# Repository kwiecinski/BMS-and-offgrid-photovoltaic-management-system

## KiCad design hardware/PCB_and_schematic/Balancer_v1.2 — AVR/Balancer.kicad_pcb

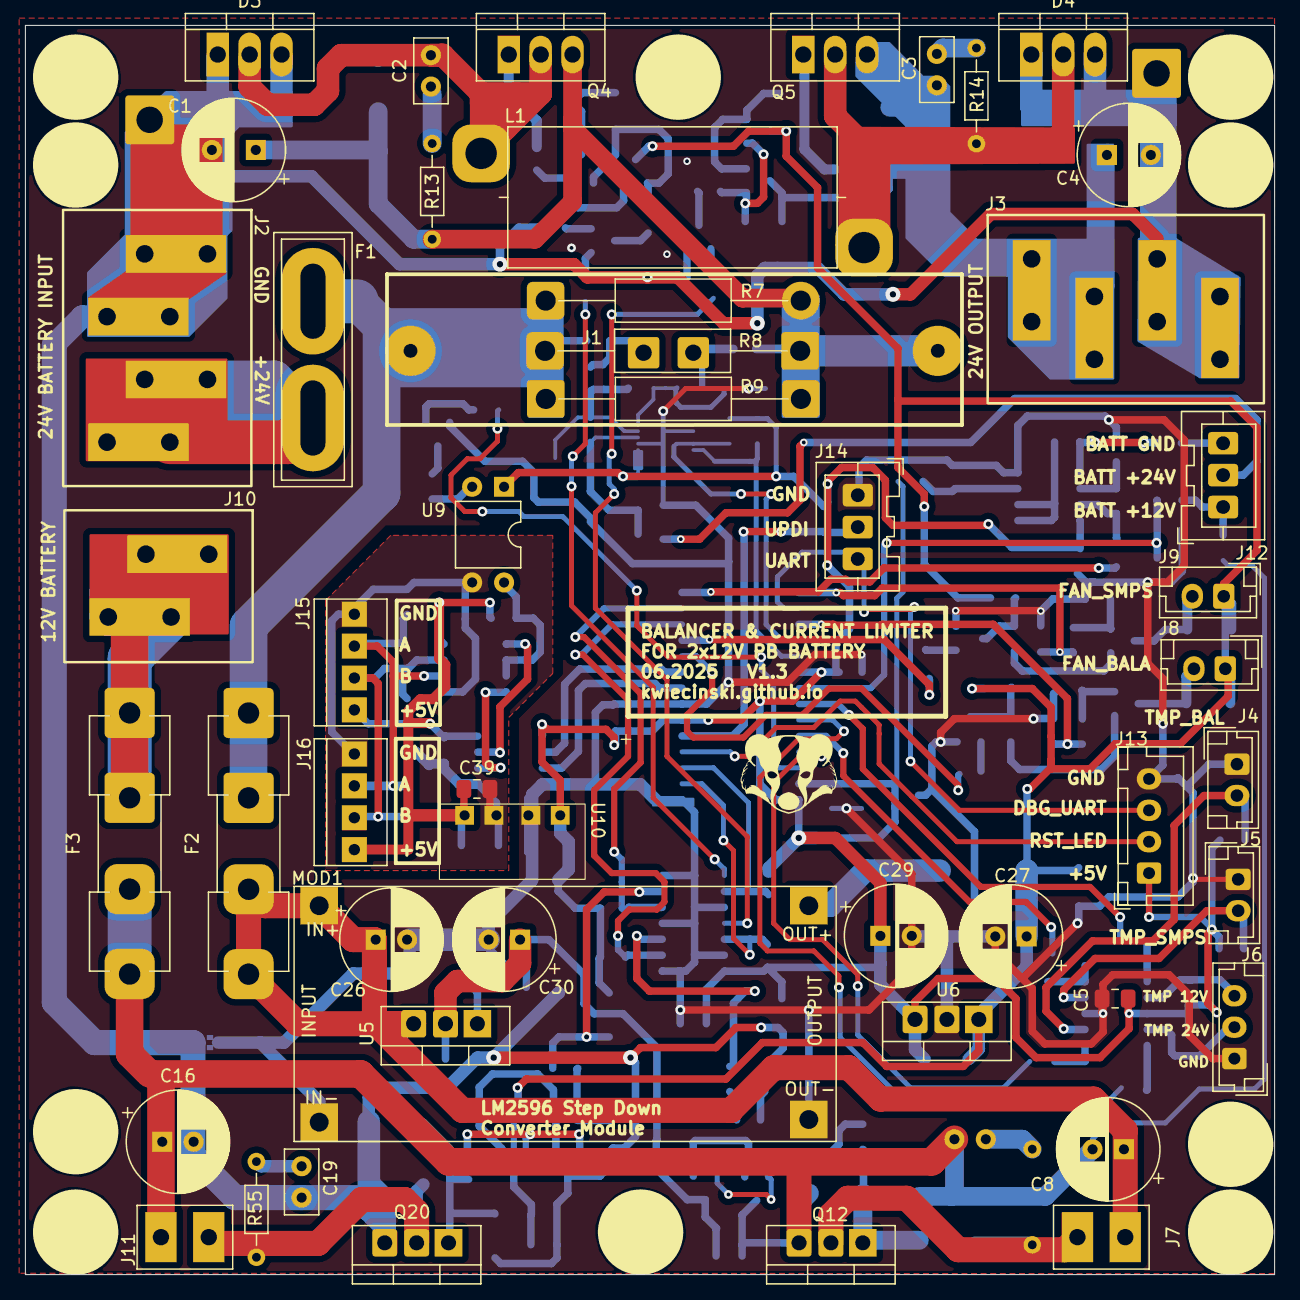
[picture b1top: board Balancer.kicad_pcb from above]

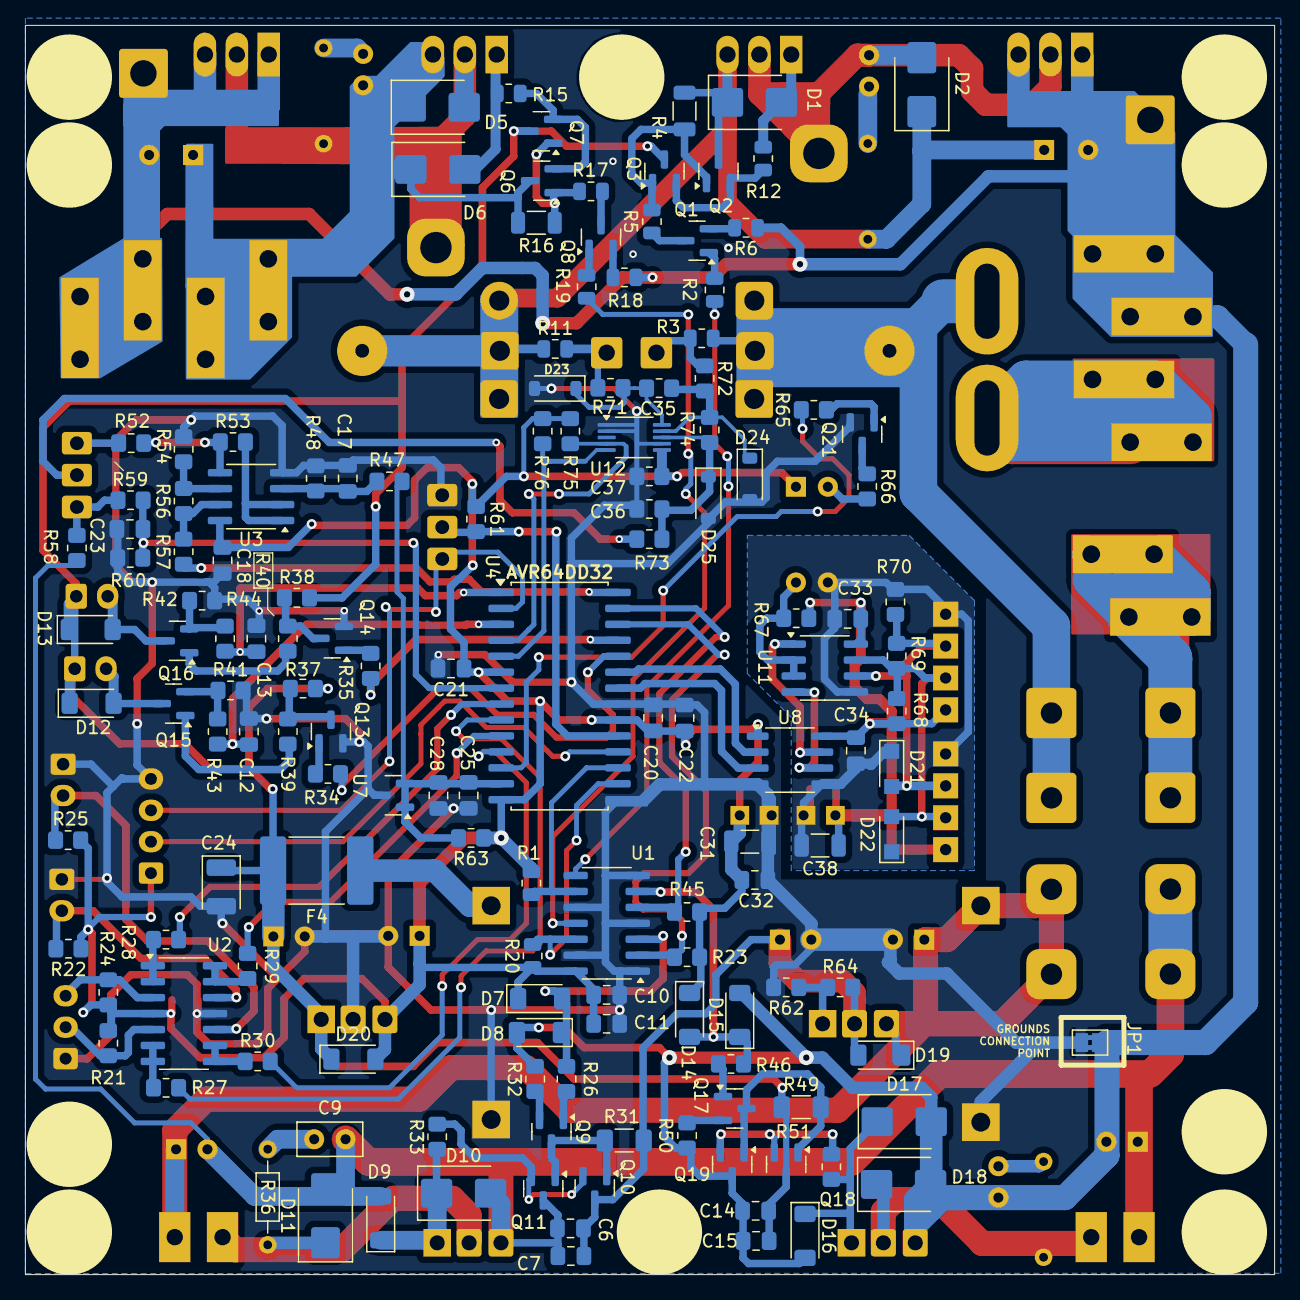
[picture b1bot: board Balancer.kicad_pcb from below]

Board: 2 copper layers, 99.5 x 99.5 mm, 208 parts (145 on the bottom side), 112 nets.

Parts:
C1, C4: 100u/35V; CP_Radial_D8.0mm_P3.50mm
C2, C3, C9, C19: 1u; C_Disc_D5.0mm_W2.5mm_P2.50mm
C5, C6, C10, C14, C17, C18, C20, C21, C28, C32, C33, C34, C39: 100n; C_0805_2012Metric_Pad1.18x1.45mm_HandSolder
C7, C15, C22, C25: 10u; C_0805_2012Metric_Pad1.18x1.45mm_HandSolder
C8, C16: 470u/25V; CP_Radial_D8.0mm_P2.50mm
C11: 1u; C_0805_2012Metric_Pad1.18x1.45mm_HandSolder
C12, C13: 47n; C_0805_2012Metric_Pad1.18x1.45mm_HandSolder
C23: 470n; C_0805_2012Metric_Pad1.18x1.45mm_HandSolder
C24: 100u/6,3V (JA8); CP_EIA-3528-21_Kemet-B
C26: 220u/35V; CP_Radial_D8.0mm_P2.50mm
C27: 470u/16V; CP_Radial_D8.0mm_P2.50mm
C29: 220u/6,3V; CP_Radial_D8.0mm_P2.50mm
C30: 100u/25V; CP_Radial_D8.0mm_P2.50mm
C31, C38: 10u; C_1206_3216Metric
C35, C36, C37: 100n; R_0805_2012Metric_Pad1.20x1.40mm_HandSolder
D1, D2, D5, D6, D10, D11, D17, D18: SM6T15A; D_SMB
D3, D4: TO-220-3_V_Thick_Pads
D7, D8, D9, D12, D13, D14, D15, D16: BAT86; D_MiniMELF
D19, D20: 1N4148; D_MiniMELF
D21, D22: D_TVS; Nexperia_CFP3_SOD-123W
D23, D24, D25: PTVS5V0Z1USK; D_SOD-123
F1: 6,3A; Fuse_Blade_ATO_directSolder
F2: 2A; Fuseholder_Clip-5x20mm_Eaton_1A5601-01_Inline_P20.80x6.76mm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
F3: 6,3A; Fuseholder_Clip-5x20mm_Eaton_1A5601-01_Inline_P20.80x6.76mm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
F4: 2A; Fuse_2920_7451Metric_Pad2.10x5.45mm_HandSolder
H1, H2, H3, H4, H5, H6, H7, H8, H9, H10: MountingHole; Mount-Hole-3mm
J1: External Current Shunt; Hirose_DF63M-2P-3.96DSA_1x02_P3.96mm_Vertical
J2: BATT_IN; Flat-6,3mm-connector-4P
J3: BATT_OUT; Flat-6,3mm-connector-4P
J4: TMP_BALANCER; JST_EH_B2B-EH-A_1x02_P2.50mm_Vertical
J5: TMP_SMPS; JST_EH_B2B-EH-A_1x02_P2.50mm_Vertical
J6: THERMISTOR_BATT; JST_EH_B3B-EH-A_1x03_P2.50mm_Vertical
J7, J11: LOAD_RESISTOR; Conn_1x2_wire
J8: FAN_BALANCER; JST_EH_B2B-EH-A_1x02_P2.50mm_Vertical
J9: FAN_SMPS; JST_EH_B2B-EH-A_1x02_P2.50mm_Vertical
J10: BATT_12V; Flat-6,3mm-connector-2P
J12: Conn_01x03; JST_XA_1x03_P2.54mm_Vertical
J13: LED; JST_XH_B4B-XH-A_1x04_P2.50mm_Vertical
J14: ICP; JST_XA_1x03_P2.54mm_Vertical
J15, J16: RS485; Conn-01x04-N25-W4P
J17: Conn_01x01; SolderWire-1.5sqmm_1x01_D1.7mm_OD3.9mm
J18: SolderWire-1.5sqmm_1x01_D1.7mm_OD3.9mm
JP1: GND_Bridged; SolderJumper-2_P1.3mm_Bridged2Bar_Pad1.0x1.5mm
L1: L; Inductor_Toroidal
MOD1: LM2596-Step-Down; LM2596-Step-Down-Conv
Q1, Q2, Q6, Q8, Q9, Q10, Q13, Q14, Q17, Q18, Q21: BC817; SOT-23
Q3, Q7, Q11, Q19: BC807; SOT-23
Q4, Q5: IRF4905; TO-220-3_V_Thick_Pads
Q12, Q20: IRF540N; TO-220-3_Vertical-little-bigger pads
Q15, Q16: AO3400A; SOT-23
R1, R20: 10k; R_0805_2012Metric
R2, R5, R17, R19: 1k; R_0805_2012Metric
R3, R11: 0R; R_0805_2012Metric
R4, R16: 10k; R_1206_3216Metric
R6, R18: 100R; R_0805_2012Metric
R7, R8, R9: 20A/75mV; R_Axial_DIN0309_L9.0mm_D3.2mm_P20.32mm_Horizontal
R10: 20A/75mV; Resistor-Power-5W-L22-W10
R12, R15: 10R; R_0805_2012Metric
R13, R14, R36, R55: 10R; R_Axial_DIN0204_L3.6mm_D1.6mm_P7.62mm_Horizontal
R21, R22, R24, R25: 150k; R_0805_2012Metric_Pad1.20x1.40mm_HandSolder
R23, R34, R35, R37, R38, R45, R61, R75, R76: 10k; R_0805_2012Metric_Pad1.20x1.40mm_HandSolder
R26, R27, R28, R29, R30, R43, R44, R46, R60, R62, R64, R65, R66: 1k; R_0805_2012Metric_Pad1.20x1.40mm_HandSolder
R31, R49: 2k2; R_1206_3216Metric_Pad1.30x1.75mm_HandSolder
R32: 470R; R_0805_2012Metric_Pad1.20x1.40mm_HandSolder
R33, R51, R71, R72, R73: 10R; R_0805_2012Metric_Pad1.20x1.40mm_HandSolder
R39, R40, R57: 100R; R_0805_2012Metric_Pad1.20x1.40mm_HandSolder
R41, R42: 210mR; R_0805_2012Metric_Pad1.20x1.40mm_HandSolder
R47, R48, R52, R53, R54, R56: 10k/1%; R_0805_2012Metric_Pad1.20x1.40mm_HandSolder
R50: 220R; R_0805_2012Metric_Pad1.20x1.40mm_HandSolder
R58, R74: 0R; R_0805_2012Metric_Pad1.20x1.40mm_HandSolder
R59: 6k8; R_0805_2012Metric_Pad1.20x1.40mm_HandSolder
R63, R68, R70: 510R; R_0805_2012Metric_Pad1.20x1.40mm_HandSolder
R67: 4k7; R_0805_2012Metric_Pad1.20x1.40mm_HandSolder
R69: 120R; R_0805_2012Metric_Pad1.20x1.40mm_HandSolder
U1: 74AHCT125; SOIC-14_3.9x8.7mm_P1.27mm
U2: LM324; SOIC-14_3.9x8.7mm_P1.27mm
U3: LMV358; SOIC-8_3.9x4.9mm_P1.27mm
U4: AVR64DD28; SOIC-28W_7.5x17.9mm_P1.27mm
U5: LM317_TO-220; TO-220-3_Vertical-little-bigger pads
U6: LM7805_TO220; TO-220-3_Vertical-little-bigger pads
U7: TL432DBZ; SOT-23
U8: ADUM3211ARZ; SO-8_3.9x4.9mm_P1.27mm
U9: PC817; DIP-4_W7.62mm
U10: B0505S-1W; B0505S
U11: ST485; SOIC-8_3.9x4.9mm_P1.27mm
U12: INA226; VSSOP-10_3x3mm_P0.5mm

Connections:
+5V: C5.1, C10.1, C11.1, C18.1, C20.1, C21.1, C22.1, C29.1, C31.1, C32.1, C37.1, D7.1 (A1), D14.1 (A1), D20.2 (A), J13.1, R1.1, R20.1, R21.1, R22.1, R23.1, R24.1, R25.1, R45.1, R61.1, R63.1, R75.1, R76.1, U1.14 (VCC), U2.4 (V+), U3.8 (V+), U4.6 (VDDIO2), U4.14 (VDD), U4.20 (VDD), U6.3 (VO), U8.1 (VDD1), U9.1, U10.1 (GND), U12.6 (VS)
+5V_RS485: C33.1, C34.1, C38.1, C39.1, J15.1, J16.1, R67.1, R68.1, U8.8 (VDD2), U10.4 (VOUT), U11.8 (VCC)
+12V_LOCAL: C14.1, C15.1, C24.1, C27.1, D12.1 (A1), D13.1 (A1), D20.1 (K), F4.2, J8.1, J9.1, Q3.3 (C), Q7.3 (C), Q18.3 (C), R37.2, R38.2, R49.1, U6.1 (VI)
+24V_LOCAL: C6.1, C7.1, C30.1, D19.2 (A), Q10.3 (C), R31.1, R64.2, U5.2 (VO)
+BATT_12V: C6.2, C7.2, C8.2, C9.2, C16.1, D9.2 (A2), D10.2 (A2), D11.2 (A2), F3.1, J11.1, Q11.3 (C), Q12.3 (S), R58.1
+BATT_24V: C8.1, C26.1, D19.1 (K), F2.1, J7.1, MOD1.2 (IN+), U5.3 (VI)
/BMS_microcontroller/RS485_A: D21.2 (A2), J15.3, J16.3, R69.2, R70.1, U11.6 (A)
/BMS_microcontroller/RS485_B: D22.2 (A2), J15.2, J16.2, R68.2, R69.1, U11.7 (B)
/BMS_microcontroller/VOLTAGE_BATT_12V_3W: J12.1, R58.2, R59.1
ADC_I_FAN1: C13.2, R44.2, U4.1 (PA7)
ADC_I_FAN2: C12.2, R43.2, U4.3 (PC1)
BALANCE_ON_12V: R45.2, U1.5, U4.27 (PA5)
BALANCE_ON_24V: R23.2, U1.2, U4.26 (PA4)
CLOCK: R76.2, U4.5 (PC3), U12.5 (SCL)
DBG_UART: J13.3, J14.3, U4.2 (PC0)
DC_LINE_24V: C3.2, C4.1, D5.1 (A1), D6.1 (A1), J3.1, J3.2, Q5.3 (S), Q6.3 (C), R16.2
GND: C5.2, C10.2, C11.2, C12.1, C13.1, C17.2, C18.2, C20.2, C21.2, C22.2, C23.2, C24.2, C25.2, C26.2, C27.2, C28.2, C29.2, C30.2, C31.2, C32.2, C36.2, C37.2, D23.2 (A), D24.2 (A), D25.2 (A), J4.1, J5.1, J6.1, J13.4, J14.1, JP1.1 (A), MOD1.1 (IN-), MOD1.3 (OUT-), Q13.2 (E), Q14.2 (E), Q21.2 (E), R41.2, R42.2, R48.2, R54.2, R60.2, R62.2, U1.1, U1.4, U1.7 (GND), U1.10, U1.13, U2.11 (V-), U3.4 (V-), U4.15 (GND), U4.21 (GND), U6.2 (GND), U7.3 (A), U8.4 (GND1), U10.2 (VIN), U12.1 (A1), U12.2 (A0), U12.7 (GND)
GNDA: C1.2, C4.2, C14.2, C15.2, C16.2, C19.2, D3.1 (K), D3.3 (K), D4.1 (K), D4.3 (K), D8.2 (A2), D15.2 (A2), D16.2 (A), D17.2 (A2), D18.2 (A2), J2.1, J2.2, J3.3, J3.4, J17.1, J18.1, JP1.2 (B), Q19.3 (C), Q20.3 (S), R6.1, R18.2, R32.2, R50.2
GND_RS485: C33.2, C34.2, C38.2, C39.2, D21.1 (A1), D22.1 (A1), J15.4, J16.4, R70.2, U8.5 (GND2), U9.3, U10.3 (0V), U11.5 (GND)
GND_VOLTAGE_DROP_ADC: R57.1, U4.28 (P6)
GND_VOLTAGE_DROP_INPUT: J12.3, R52.2
LED1_PF6_RST: J13.2, U4.18 (PF6(RST))
unnamed: C2.1, R13.2
unnamed: C3.1, R14.2
unnamed: C9.1, R36.2
unnamed: C19.1, R55.2
unnamed: C1.1, D1.1 (A1), D2.1 (A1), Q2.3 (C), Q4.3 (S), R4.2, R7.2, R8.2, R9.2, R10.2, R11.1, R13.1
unnamed: D1.2 (A2), Q4.1 (G), R12.2
unnamed: C2.2, D2.2 (A2), D3.2 (A), L1.1, Q4.2 (D)
unnamed: D4.2 (A), D5.2 (A2), L1.2, Q5.2 (D), R14.1
unnamed: D6.2 (A2), Q5.1 (G), R15.2
unnamed: D7.2 (A2), D8.1 (A1), R26.2, U1.3
unnamed: D9.1 (A1), D10.1 (A1), Q12.1 (G), R33.1
unnamed: D11.1 (A1), J7.2, Q12.2 (D), R36.1
unnamed: D12.2 (A2), J8.2, Q15.3 (D)
unnamed: D13.2 (A2), J9.2, Q16.3 (D)
unnamed: D14.2 (A2), D15.1 (A1), R46.2, U1.6
unnamed: D16.1 (K), D17.1 (A1), Q20.1 (G), R51.1
unnamed: D18.1 (A1), J11.2, Q20.2 (D), R55.1
unnamed: C35.1, D23.1 (K), R71.2, U12.10 (Vin+)
unnamed: C35.2, D24.1 (K), R72.2, R74.1, U12.9 (Vin-)
unnamed: C36.1, D25.1 (K), R73.2, R74.2, U12.8 (Vbus)
unnamed: F1.2, F2.2, R3.1, R7.1, R8.1, R9.1, R10.1
unnamed: F1.1, J2.3, J2.4
unnamed: J4.2, R25.2, U2.10 (+)
unnamed: J5.2, R22.2, U2.12 (+)
unnamed: J6.2, R21.2, U2.5 (+)
unnamed: J6.3, R24.2, U2.3 (+)
unnamed: F3.2, J10.1, J10.2
unnamed: F4.1, MOD1.4 (OUT+)
unnamed: Q1.1 (B), R2.2
unnamed: Q1.3 (C), R5.1
unnamed: Q1.2 (E), R6.2
unnamed: Q2.1 (B), Q3.1 (B), R4.1, R5.2
unnamed: Q2.2 (E), Q3.2 (E), R12.1
unnamed: Q6.1 (B), Q7.1 (B), R16.1, R17.2
unnamed: Q6.2 (E), Q7.2 (E), R15.1
unnamed: Q8.1 (B), R19.2
unnamed: Q8.3 (C), R17.1
unnamed: Q8.2 (E), R18.1
unnamed: Q9.1 (B), R26.1
unnamed: Q9.2 (E), R32.1
unnamed: Q9.3 (C), Q10.1 (B), Q11.1 (B), R31.2
unnamed: Q10.2 (E), Q11.2 (E), R33.2
unnamed: Q13.1 (B), R34.2
unnamed: Q13.3 (C), R37.1, R39.1
unnamed: Q14.1 (B), R35.2
unnamed: Q14.3 (C), R38.1, R40.1
unnamed: Q15.1 (G), R39.2
unnamed: Q15.2 (S), R41.1, R43.1
unnamed: Q16.1 (G), R40.2
unnamed: Q16.2 (S), R42.1, R44.1
unnamed: Q17.1 (B), R46.1
unnamed: Q17.3 (C), Q18.1 (B), Q19.1 (B), R49.2
unnamed: Q17.2 (E), R50.1
unnamed: Q18.2 (E), Q19.2 (E), R51.2
unnamed: Q21.1 (B), R65.2
unnamed: Q21.3 (C), R66.1
unnamed: R2.1, U1.8
unnamed: R19.1, U1.11
unnamed: R56.1, R57.2, U3.7
unnamed: R66.2, U9.2
unnamed: R28.1, U2.1, U2.2 (-)
unnamed: R27.1, U2.6 (-), U2.7
unnamed: R30.1, U2.8, U2.9 (-)
unnamed: R29.1, U2.13 (-), U2.14
unnamed: C17.1, R47.2, R48.1, U3.3 (+)
unnamed: R53.2, U3.1, U3.2 (-)
unnamed: R52.1, R53.1, U3.5 (+)
unnamed: R54.1, R56.2, U3.6 (-)
unnamed: R62.1, R64.1, U5.1 (ADJ)
unnamed: R67.2, U9.4, U11.2 (~RE), U11.3 (DE)
unnamed: U8.6 (VOB), U11.4 (DI)
unnamed: U8.7 (VIA), U11.1 (RO)
PWM_FAN_BALANCER: R34.1, U4.24 (PA2)
PWM_FAN_SMPS: R35.1, U4.25 (PA3)
PWM_OUT_CHRG: R20.2, U1.12, U4.16 (PF0)
PWM_OUT_DISCH: R1.2, U1.9, U4.17 (PF1)
RS232_RX: U4.23 (PA1), U8.2 (VOA)
RS232_TX: U4.22 (PA0), U8.3 (VIB)
RS485_OUTPUT_ENABLE: R65.1, U4.12 (PD6)
R_shunt_H: J1.2, R3.2, R72.1
R_shunt_L: J1.1, R11.2, R71.1
SDA: R75.2, U4.4 (PC2), U12.4 (SDA)
TEMP_AKU_12V: R28.2, U4.8 (PD2)
TEMP_AKU_24V: R27.2, U4.9 (PD3)
TEMP_BALANCER: R30.2, U4.11 (PD5)
TEMP_SMPS: R29.2, U4.10 (PD4)
UPDI: J14.2, R61.2, U4.19 (PF7(UPDI))
VOLTAGE_BATT_12V: C23.1, R59.2, R60.1, U4.7 (PD1)
VOLTAGE_BATT_24V_3W: J12.2, R73.1
VREF: C25.1, C28.1, R47.1, R63.2, U4.13 (PD7), U7.1 (REF), U7.2 (K)

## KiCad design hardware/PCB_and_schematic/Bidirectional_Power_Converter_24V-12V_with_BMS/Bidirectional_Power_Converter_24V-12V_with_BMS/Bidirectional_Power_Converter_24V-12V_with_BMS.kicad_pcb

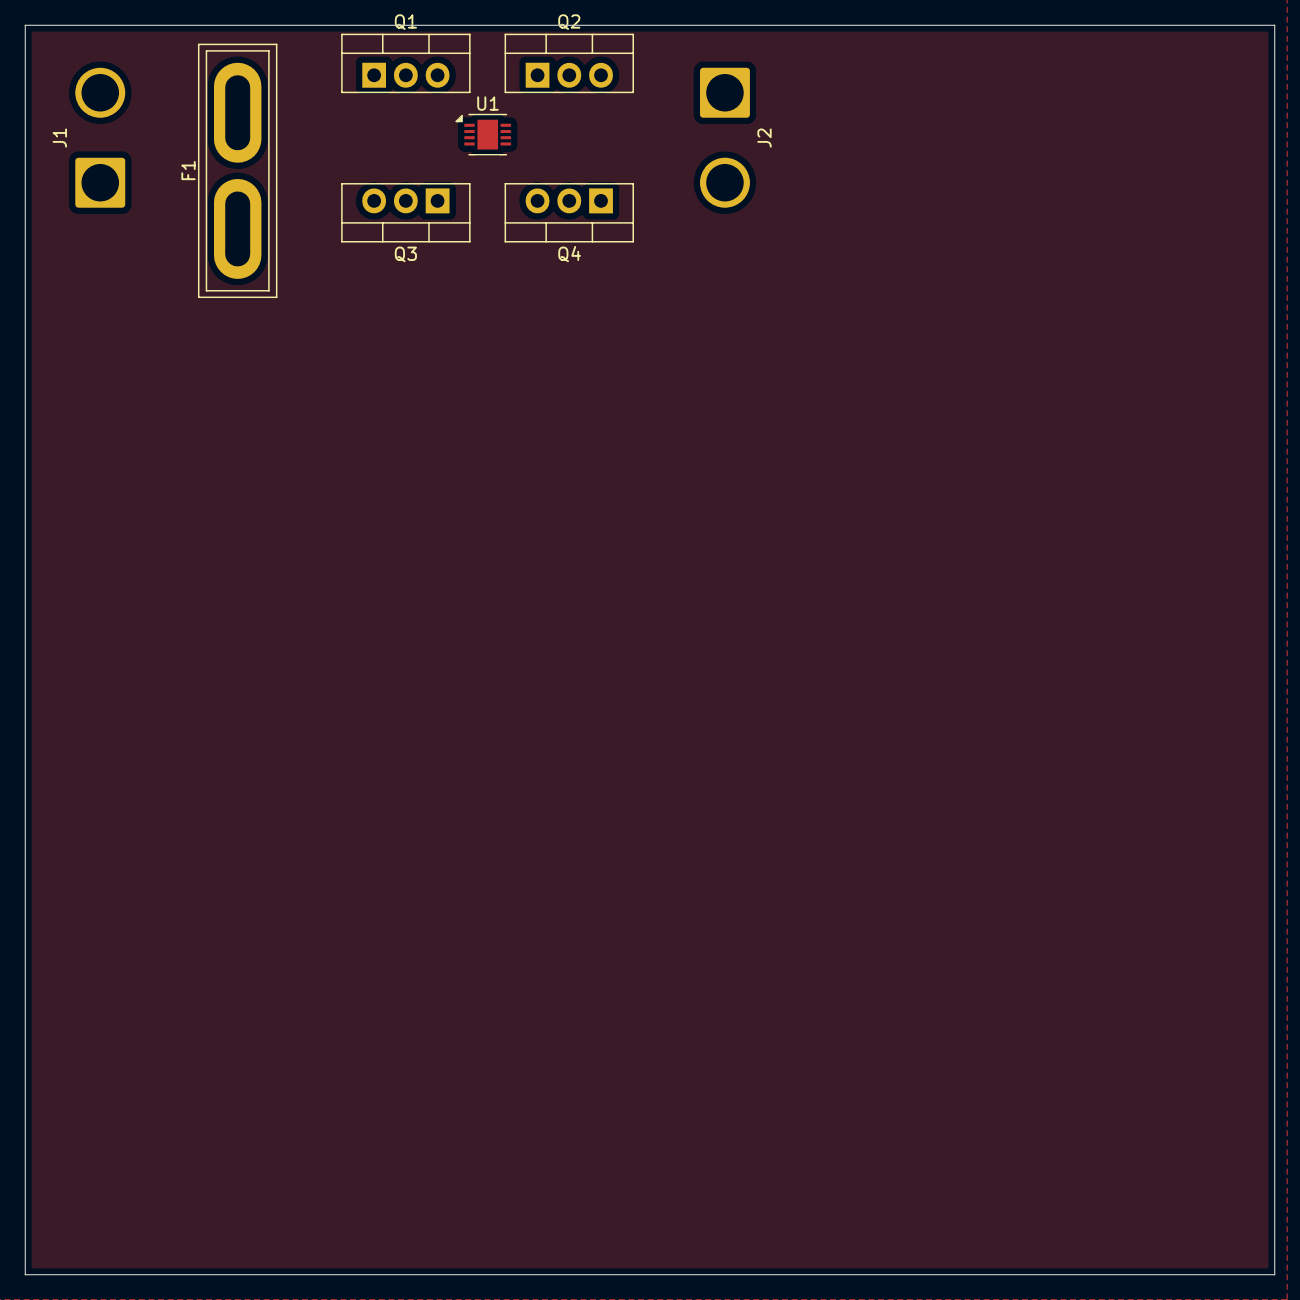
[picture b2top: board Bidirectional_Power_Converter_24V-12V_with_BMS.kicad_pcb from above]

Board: 2 copper layers, 100.0 x 100.0 mm, 8 parts (0 on the bottom side), 9 nets, no tracks yet.

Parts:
F1: 20A; Fuse_Blade_ATO_directSolder
J1: AC_IN; SolderWire-2.5sqmm_1x02_P7.2mm_D2.4mm_OD3.6mm
J2: DC_OUT; SolderWire-2.5sqmm_1x02_P7.2mm_D2.4mm_OD3.6mm
Q1, Q2, Q3, Q4: IRF540N; TO-220-3_Vertical
U1: LT4320xDD-1; DFN-8-1EP_3x3mm_P0.5mm_EP1.65x2.38mm

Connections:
unnamed: J1.1, Q3.2 (D), Q4.3 (S), U1.1 (IN2)
unnamed: F1.1, J1.2
unnamed: J2.1, Q2.2 (D), Q3.3 (S), U1.6 (OUTP)
unnamed: J2.2, Q1.3 (S), Q4.2 (D), U1.5 (OUTN), U1.9 (OUTN)
unnamed: F1.2, Q1.2 (D), Q2.3 (S), U1.8 (IN1)
unnamed: Q1.1 (G), U1.3 (BG2)
unnamed: Q2.1 (G), U1.7 (TG1)
unnamed: Q3.1 (G), U1.2 (TG2)
unnamed: Q4.1 (G), U1.4 (BG1)

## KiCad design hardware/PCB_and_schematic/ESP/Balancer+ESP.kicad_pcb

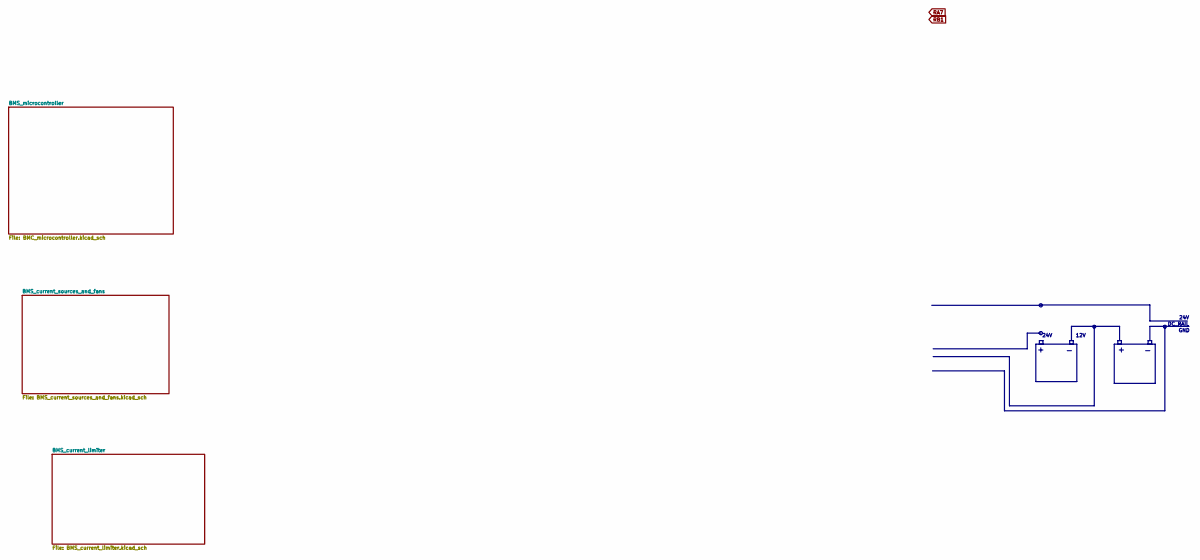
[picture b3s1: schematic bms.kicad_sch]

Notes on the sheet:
GND
12V
24V
DC_RAIL

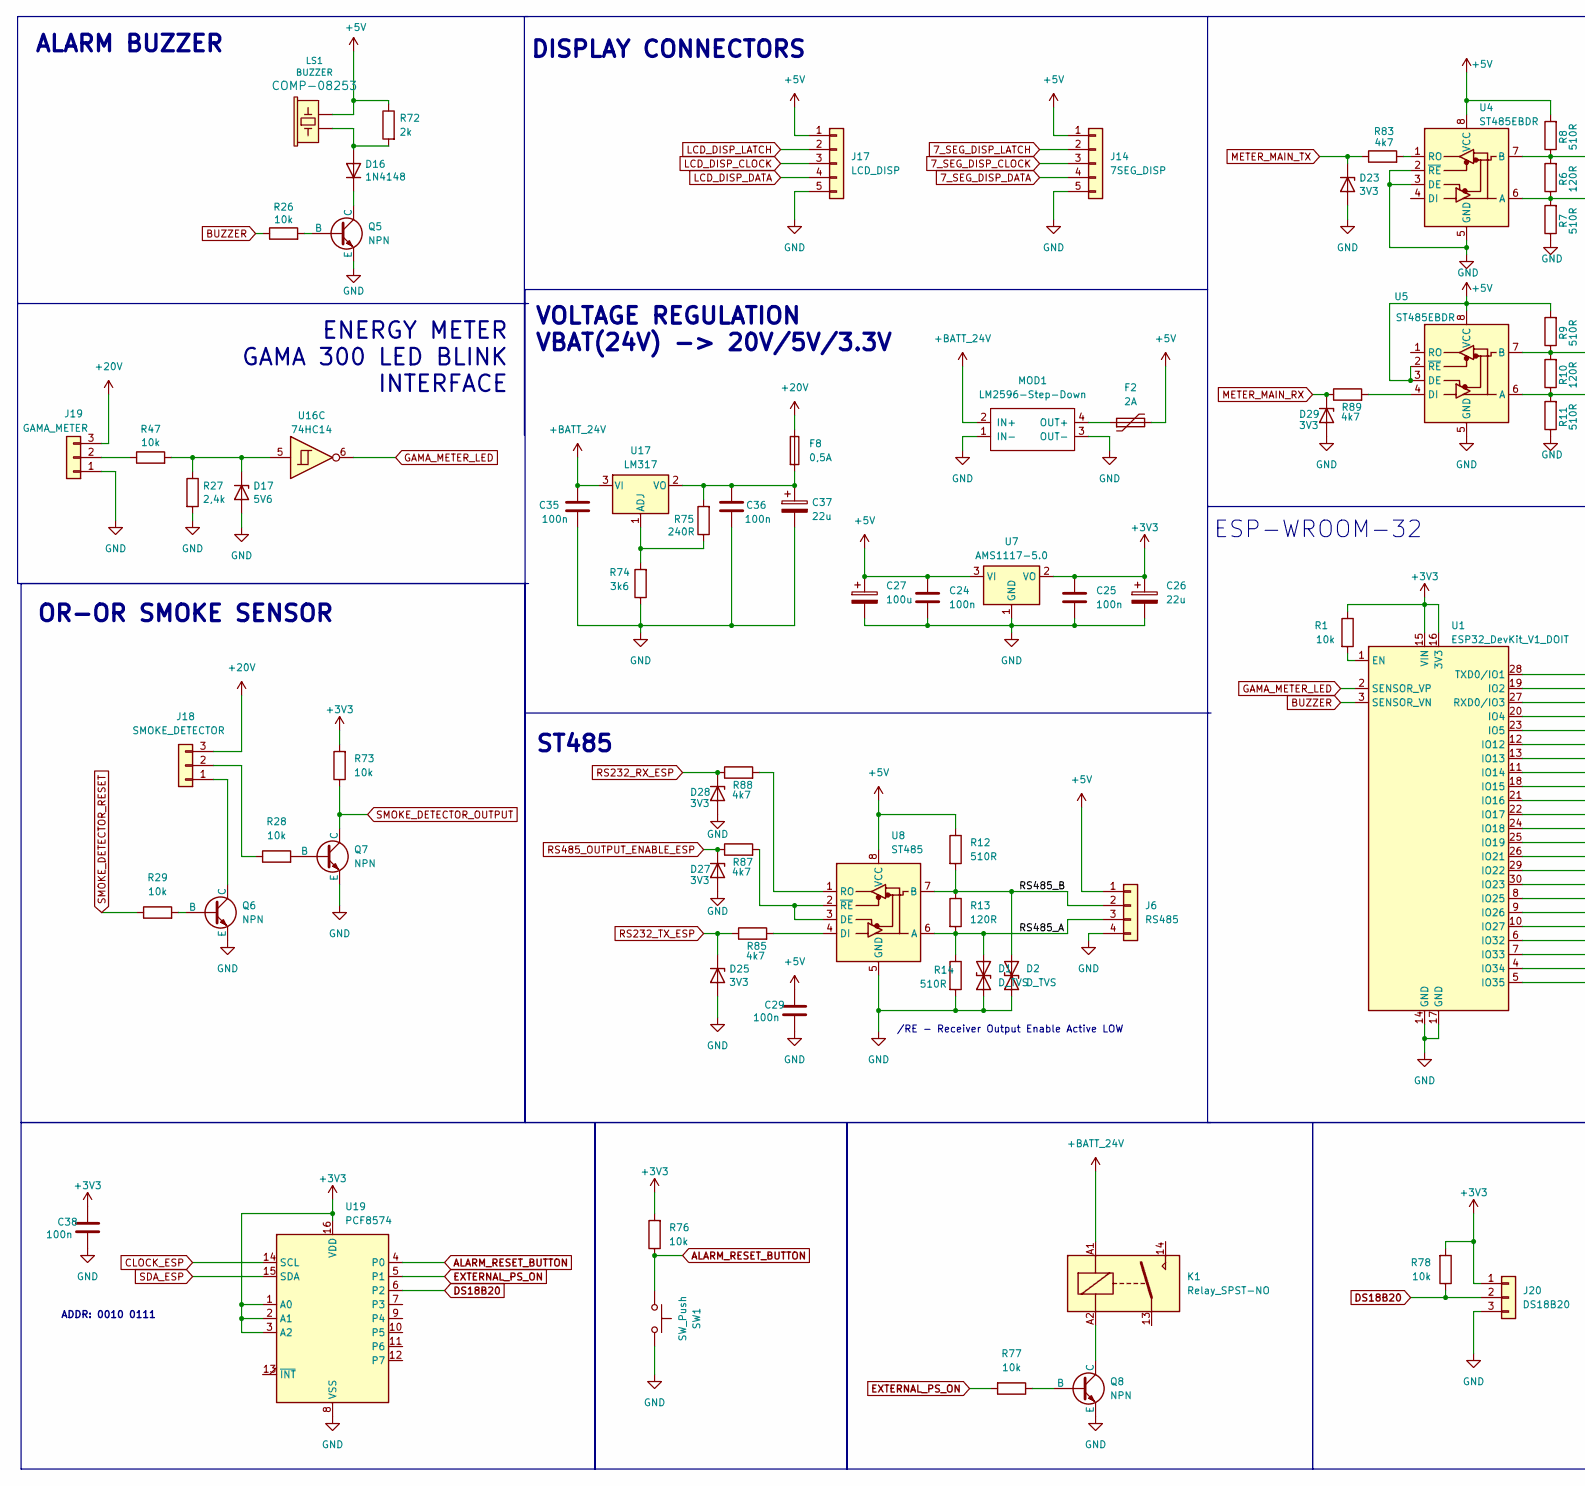
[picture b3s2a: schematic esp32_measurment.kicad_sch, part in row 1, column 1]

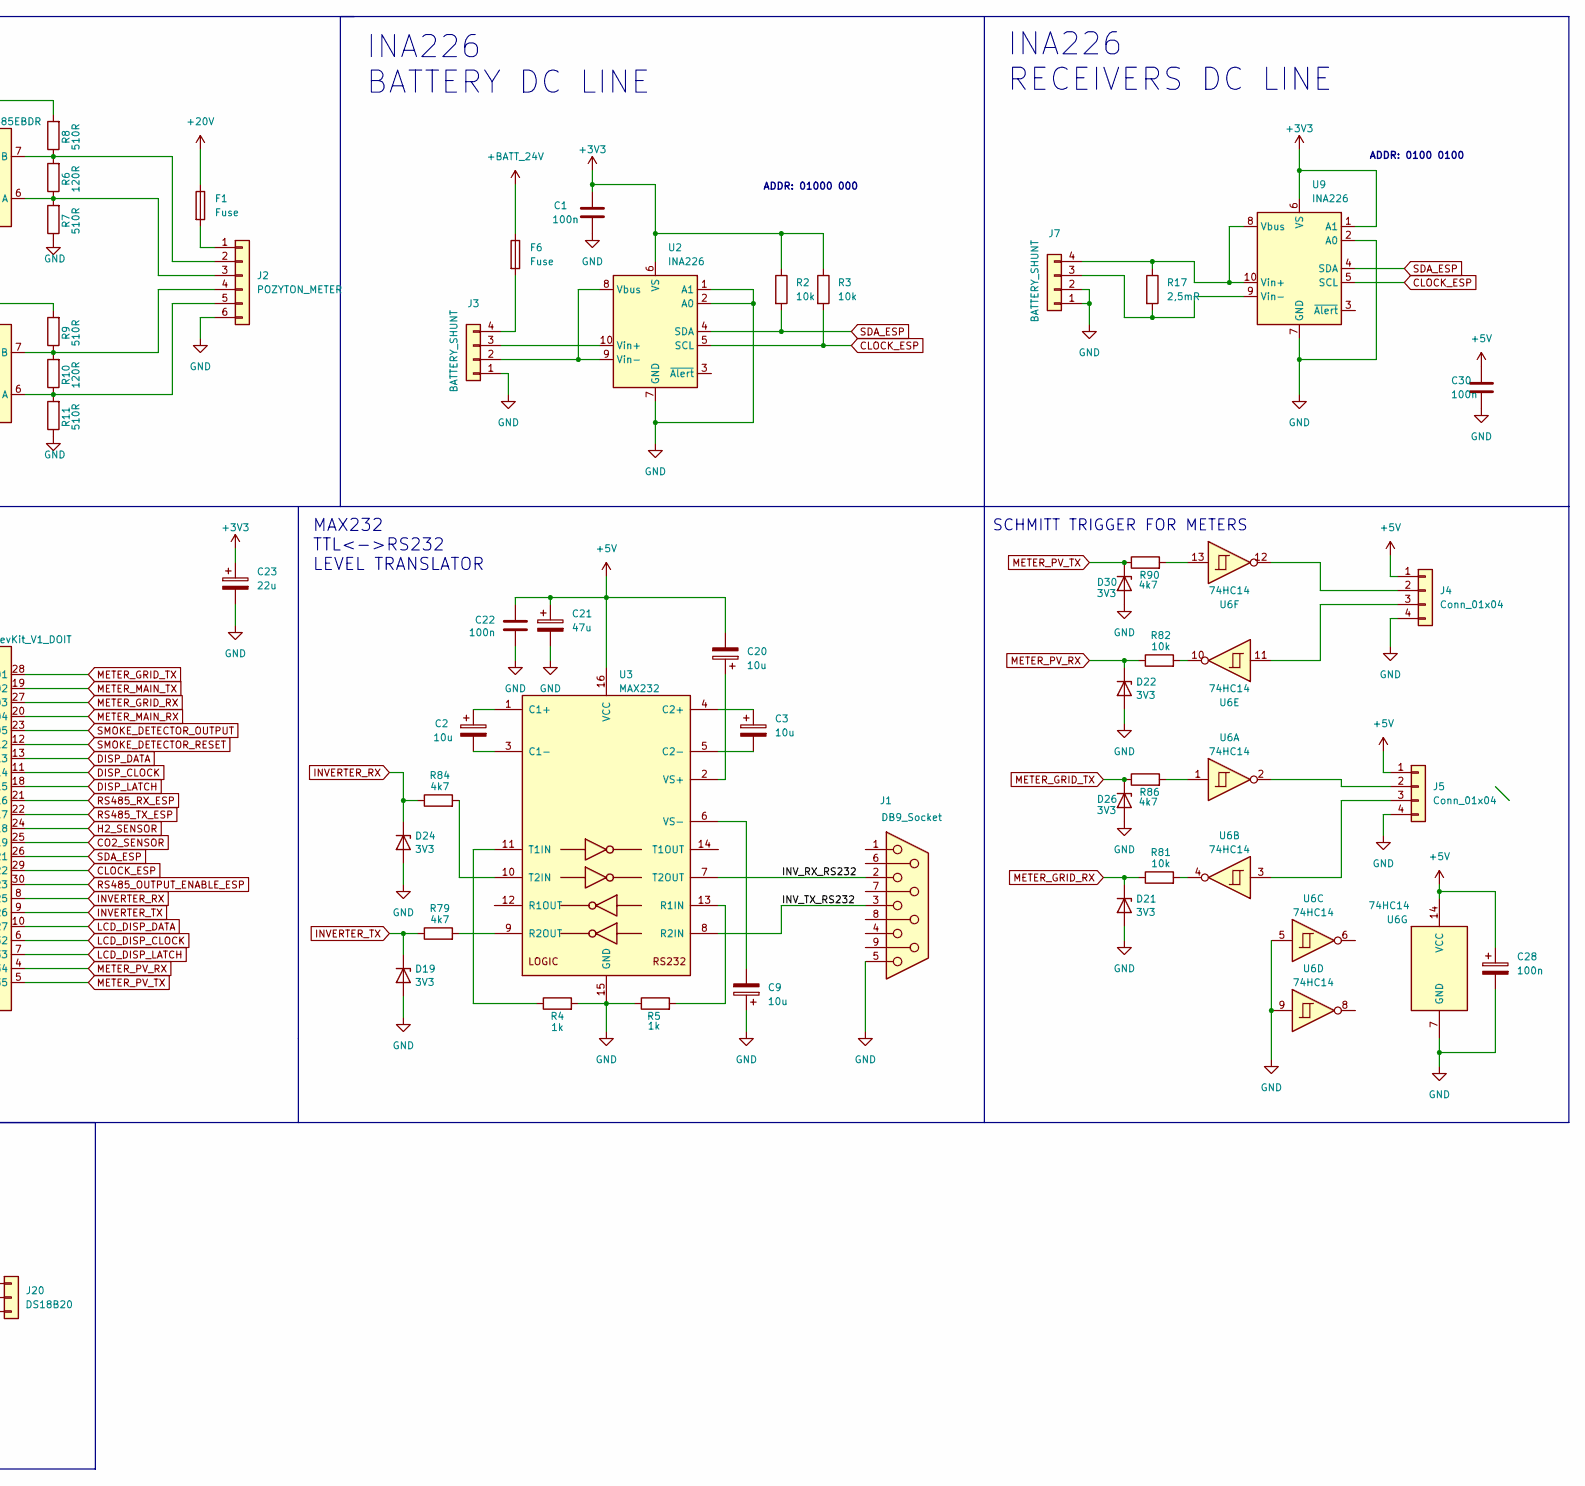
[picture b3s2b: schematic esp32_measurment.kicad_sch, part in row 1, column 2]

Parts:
C1, C30: 100n; R_0805_2012Metric_Pad1.20x1.40mm_HandSolder
C2, C3, C9, C20: 10u; CP_Radial_D5.0mm_P2.00mm
C21: 47u; CP_Radial_D5.0mm_P2.00mm
C22: 100n; CP_Elec_6.3x4.5
C23: 22u; CP_Radial_D5.0mm_P2.00mm
C24, C25, C29, C35, C36, C38: 100n; C_0805_2012Metric_Pad1.18x1.45mm_HandSolder
C26, C37: 22u; CP_Radial_D4.0mm_P1.50mm
C27: 100u; CP_Radial_D4.0mm_P1.50mm
C28: 100n; C_0805_2012Metric
D1, D2: D_TVS; D_SMC
D16: 1N4148; D_MiniMELF
D17: 5V6; D_MiniMELF
D19, D21, D22, D23, D24, D25, D26, D27, D28, D29, D30: 3V3; D_MiniMELF
F1: Fuse; Fuseholder_Clip-5x20mm_Littelfuse_519_Inline_P20.60x5.00mm_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
F2: 2A; Fuse_2512_6332Metric_Pad1.52x3.35mm_HandSolder
F6: Fuse; Fuseholder_Clip-5x20mm_Littelfuse_520_Inline_P20.50x5.80mm_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
F8: 0,5A; Fuseholder_Clip-5x20mm_Littelfuse_519_Inline_P20.60x5.00mm_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
J1: DB9_Socket; DSUB-9_Female_Horizontal_P2.77x2.84mm_EdgePinOffset7.70mm_H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
J2: POZYTON_METER; JST_EH_B6B-EH-A_1x06_P2.50mm_Vertical
J3, J7: BATTERY_SHUNT; JST_EH_B4B-EH-A_1x04_P2.50mm_Vertical
J4, J5: Conn_01x04; JST_EH_B4B-EH-A_1x04_P2.50mm_Vertical
J6: RS485; PinHeader_1x04_P2.54mm_Vertical
J14: 7SEG_DISP; JST_EH_B5B-EH-A_1x05_P2.50mm_Vertical
J17: LCD_DISP; JST_EH_B5B-EH-A_1x05_P2.50mm_Vertical
J18: SMOKE_DETECTOR; PinHeader_1x03_P2.54mm_Vertical
J19: GAMA_METER; PinHeader_1x03_P2.54mm_Vertical
J20: DS18B20; PinHeader_1x03_P2.54mm_Vertical
K1: Relay_SPST-NO; Relay_SPST_Omron-G5Q-1A
LS1: BUZZER; Buzzer
MOD1: LM2596-Step-Down; MP1504_Mini_3A_Step_Down_Conv
Q5, Q6, Q7, Q8: NPN; TO-92_Inline_Wide
R1, R2, R3, R26, R28, R29, R47, R73, R76, R77, R78, R81, R82: 10k; R_0805_2012Metric_Pad1.20x1.40mm_HandSolder
R4, R5: 1k; R_0805_2012Metric_Pad1.20x1.40mm_HandSolder
R6, R10, R13: 120R; R_0805_2012Metric_Pad1.20x1.40mm_HandSolder
R7, R8, R9, R11, R12, R14: 510R; R_0805_2012Metric_Pad1.20x1.40mm_HandSolder
R17: 2,5mR; R_0805_2012Metric_Pad1.20x1.40mm_HandSolder
R27: 2,4k; R_0805_2012Metric_Pad1.20x1.40mm_HandSolder
R72: 2k; 0805
R74: 3k6; R_0805_2012Metric_Pad1.20x1.40mm_HandSolder
R75: 240R; R_0805_2012Metric_Pad1.20x1.40mm_HandSolder
R79, R83, R84, R85, R86, R87, R88, R89, R90: 4k7; R_0805_2012Metric_Pad1.20x1.40mm_HandSolder
SW1: SW_Push; PinHeader_1x02_P2.54mm_Vertical
U1: ESP32_DevKit_V1_DOIT; esp32_devkit_v1_doit
U2, U9: INA226; VSSOP-10_3x3mm_P0.5mm
U3: MAX232; SOIC-16W_5.3x10.2mm_P1.27mm
U4, U5: ST485EBDR; SOIC-8_3.9x4.9mm_P1.27mm
U6, U16: 74HC14; SOIC-14_3.9x8.7mm_P1.27mm
U7: AMS1117-5.0; SOT-223-3_TabPin2
U8: ST485; SOIC-8_3.9x4.9mm_P1.27mm
U17: LM317; TO-220-3_Vertical
U19: PCF8574; DIP-16_W7.62mm_LongPads

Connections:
7_SEG_DISP_CLOCK: J14.3
7_SEG_DISP_DATA: J14.4
7_SEG_DISP_LATCH: J14.2
+3V3: C1.1, C23.1, C25.1, C26.1, C38.1, J20.1, R1.1, R2.1, R3.1, R73.2, R76.2, R78.2, U1.15 (VIN), U1.16 (3V3), U2.6 (VS), U7.2 (VO), U9.1 (A1), U9.6 (VS), U19.1 (A0), U19.2 (A1), U19.3 (A2), U19.16 (VDD)
+5V: C20.2, C21.1, C22.2, C24.1, C27.1, C28.1, C29.1, C30.1, F2.2, J4.1, J5.1, J6.1, J14.1, J17.1, LS1.- (2), R8.2, R9.2, R12.1, R72.1, U3.16 (VCC), U4.8 (VCC), U5.2 (~RE), U5.3 (DE), U5.8 (VCC), U6.14 (VCC), U7.3 (VI), U8.8 (VCC); also elsewhere on the board
+20V: F1.1, F8.1, J18.3, J19.3
+BATT_24V: C35.1, F6.1, K1.A1, MOD1.2 (IN+), U17.3 (VI); also elsewhere on the board
/ESP32_Measurment_Board/INV_RX_RS232: J1.2, U3.7 (T2OUT)
/ESP32_Measurment_Board/INV_TX_RS232: J1.3, U3.8 (R2IN)
/ESP32_Measurment_Board/RS485_A: D1.2 (A2), J6.3, R13.2, R14.1, U8.6 (A)
/ESP32_Measurment_Board/RS485_B: D2.2 (A2), J6.2, R12.2, R13.1, U8.7 (B)
ALARM_RESET_BUTTON: R76.1, SW1.1, U19.4 (P0)
BUZZER: R26.1, U1.3 (SENSOR_VN)
CLOCK_ESP: R3.2, U1.29 (IO22), U2.5 (SCL), U9.5 (SCL), U19.14 (SCL)
CO2_SENSOR: U1.25 (IO19)
DISP_CLOCK: U1.11 (IO14)
DISP_DATA: U1.13 (IO13)
DISP_LATCH: U1.18 (IO15)
DS18B20: J20.2, R78.1, U19.6 (P2)
EXTERNAL_PS_ON: R77.2, U19.5 (P1)
GAMA_METER_LED: U1.2 (SENSOR_VP), U16.6
GND: C1.2, C9.1, C21.2, C22.1, C23.2, C24.2, C25.2, C26.2, C27.2, C28.2, C29.2, C30.2, C35.2, C36.2, C37.2, C38.2, D1.1 (A1), D2.1 (A1), D17.2 (A), D19.2 (A), D21.2 (A), D22.2 (A), D23.2 (A), D24.2 (A), D25.2 (A), D26.2 (A), D27.2 (A), D28.2 (A), D29.2 (A), D30.2 (A), J1.5, J2.6, J3.1, J4.4, J5.4, J6.4, J7.1, J7.2, J14.5, J17.5, J19.1, J20.3, MOD1.1 (IN-), MOD1.3 (OUT-), Q5.3 (E), Q6.3 (E), Q7.3 (E), Q8.3 (E), R4.2, R5.1, R7.1, R11.1, R14.2, R27.2, R74.1, SW1.2, U1.14 (GND), U1.17 (GND), U2.1 (A1), U2.2 (A0), U2.7 (GND), U3.15 (GND), U4.2 (~RE), U4.3 (DE), U4.5 (GND), U5.5 (GND), U6.5, U6.7 (GND), U6.9, U7.1 (GND), U8.5 (GND), U9.2 (A0), U9.7 (GND), U19.8 (VSS); also elsewhere on the board
H2_SENSOR: U1.24 (IO18)
INVERTER_RX: D24.1 (K), R84.1, U1.8 (IO25)
INVERTER_TX: D19.1 (K), R79.1, U1.9 (IO26)
LCD_DISP_CLOCK: J17.3, U1.6 (IO32)
LCD_DISP_DATA: J17.4, U1.10 (IO27)
LCD_DISP_LATCH: J17.2, U1.7 (IO33)
METER_GRID_RX: D21.1 (K), R81.1, U1.27 (RXD0/IO3)
METER_GRID_TX: D26.1 (K), R86.1, U1.28 (TXD0/IO1)
METER_MAIN_RX: D29.1 (K), R89.1, U1.20 (IO4)
METER_MAIN_TX: D23.1 (K), R83.1, U1.19 (IO2)
METER_PV_RX: D22.1 (K), R82.1, U1.4 (IO34)
METER_PV_TX: D30.1 (K), R90.1, U1.5 (IO35)
unnamed: D16.1 (K), Q5.1 (C)
unnamed: D16.2 (A), LS1.+ (1), R72.2
unnamed: D17.1 (K), R27.1, R47.2, U16.5
unnamed: F1.2, J2.1
unnamed: J2.2, R6.2, R8.1, U4.7 (B)
unnamed: J2.3, R6.1, R7.2, U4.6 (A)
unnamed: J2.4, R9.1, R10.2, U5.7 (B)
unnamed: J2.5, R10.1, R11.2, U5.6 (A)
unnamed: J3.2, U2.8 (Vbus), U2.9 (Vin-)
unnamed: J3.3, U2.10 (Vin+)
unnamed: F6.2, J3.4
unnamed: J4.2, U6.12
unnamed: J4.3, U6.11
unnamed: J5.2, U6.2
unnamed: J5.3, U6.3
unnamed: J7.3, R17.2, U9.9 (Vin-)
unnamed: J7.4, R17.1, U9.8 (Vbus), U9.10 (Vin+)
unnamed: J18.1, Q6.1 (C)
unnamed: J18.2, R28.1
unnamed: J19.2, R47.1
unnamed: F2.1, MOD1.4 (OUT+)
unnamed: Q5.2 (B), R26.2
unnamed: Q6.2 (B), R29.2
unnamed: Q7.2 (B), R28.2
unnamed: Q8.2 (B), R77.1
unnamed: K1.A2, Q8.1 (C)
unnamed: R81.2, U6.4
unnamed: R82.2, U6.10
unnamed: R86.2, U6.1
unnamed: R90.2, U6.13
unnamed: R1.2, U1.1 (EN)
unnamed: C2.1, U3.1 (C1+)
unnamed: C2.2, U3.3 (C1-)
unnamed: C3.1, U3.4 (C2+)
unnamed: C3.2, U3.5 (C2-)
unnamed: R5.2, U3.13 (R1IN)
unnamed: R79.2, U3.9 (R2OUT)
unnamed: R4.1, U3.11 (T1IN)
unnamed: R84.2, U3.10 (T2IN)
unnamed: C20.1, U3.2 (VS+)
unnamed: C9.2, U3.6 (VS-)
unnamed: R83.2, U4.1 (RO)
unnamed: R89.2, U5.4 (DI)
unnamed: R87.2, U8.2 (~RE), U8.3 (DE)
unnamed: R85.2, U8.4 (DI)
unnamed: R88.2, U8.1 (RO)
unnamed: R74.2, R75.1, U17.1 (ADJ)
unnamed: C36.1, C37.1, F8.2, R75.2, U17.2 (VO)
RS232_RX_ESP: D28.1 (K), R88.1
RS232_TX_ESP: D25.1 (K), R85.1
RS485_OUTPUT_ENABLE_ESP: D27.1 (K), R87.1, U1.30 (IO23)
RS485_RX_ESP: U1.21 (IO16)
RS485_TX_ESP: U1.22 (IO17)
SDA_ESP: R2.2, U1.26 (IO21), U2.4 (SDA), U9.4 (SDA), U19.15 (SDA)
SMOKE_DETECTOR_OUTPUT: Q7.1 (C), R73.1, U1.23 (IO5)
SMOKE_DETECTOR_RESET: R29.1, U1.12 (IO12)

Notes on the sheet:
SCHMITT TRIGGER FOR METERS
ADDR: 01000 000
ENERGY METER GAMA 300 LED BLINK INTERFACE
ADDR: 0010 0111
OR-OR SMOKE SENSOR
ESP-WROOM-32
INA226 RECEIVERS DC LINE
/RE - Receiver Output Enable Active LOW
MAX232 TTL<->RS232 LEVEL TRANSLATOR
DISPLAY CONNECTORS
INA226 BATTERY DC LINE
ST485
ADDR: 0100 0100
ALARM BUZZER
VOLTAGE REGULATION VBAT(24V) -> 20V/5V/3.3V
